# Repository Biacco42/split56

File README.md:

# split56
modulo seriese split keyboard

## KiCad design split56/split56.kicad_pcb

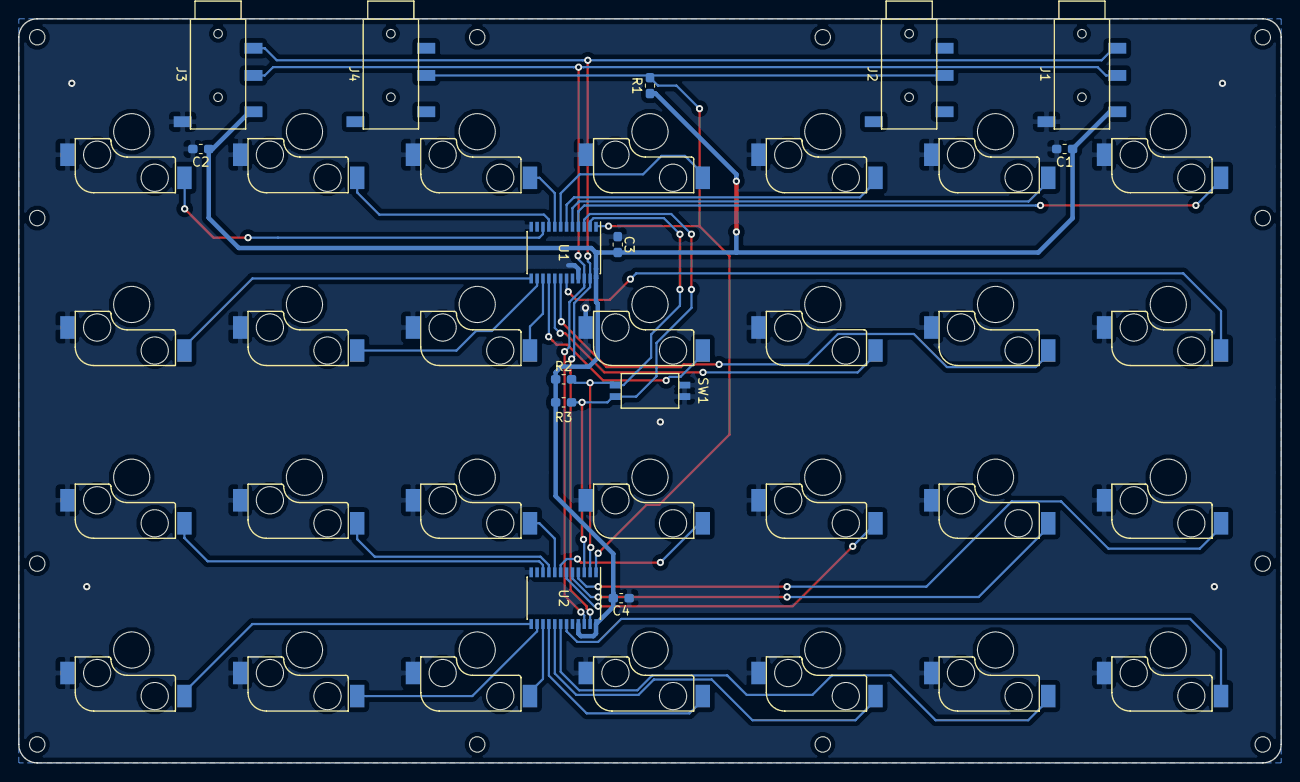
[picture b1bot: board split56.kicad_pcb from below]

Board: 2 copper layers, 139.2 x 82.0 mm, 42 parts (14 on the bottom side), 35 nets.

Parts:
C1, C2: 1 uF; C_0603_1608Metric_Pad1.05x0.95mm_HandSolder
C3, C4: 100 nF; C_0603_1608Metric_Pad1.05x0.95mm_HandSolder
J1, J2, J3, J4: AudioJack4; TRRS_SMD_PJ320
R1: 10 kΩ; R_0603_1608Metric_Pad1.05x0.95mm_HandSolder
R2, R3: 1 MΩ; R_0603_1608Metric_Pad1.05x0.95mm_HandSolder
SW1: SW_DIP_x02; DipSwitch
SW2, SW3, SW4, SW5, SW6, SW7, SW8, SW9, SW10, SW11, SW12, SW13, SW14, SW15, SW16, SW17, SW18, SW19, SW20, SW21, SW22, SW23, SW24, SW25, SW26, SW27, SW28, SW29: SW_Push; Kailh_Socket
U1, U2: TCA9555PWR; TSSOP-24_4.4x7.8mm_P0.65mm

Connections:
A1: R2.2, SW1.2, U1.2, U2.2
A2: R3.2, SW1.1, U1.3, U2.3
GND: C1.2, C2.2, C3.2, C4.2, J1.S, J3.S, SW1.3, SW1.4, SW2.1, SW3.1, SW4.1, SW5.1, SW6.1, SW7.1, SW8.1, SW9.1, SW10.1, SW11.1, SW12.1, SW13.1, SW14.1, SW15.1, SW16.1, SW17.1, SW18.1, SW19.1, SW20.1, SW21.1, SW22.1, SW23.1, SW24.1, SW25.1, SW26.1, SW27.1, SW28.1, SW29.1, U1.12, U1.21, U2.12
INT: J2.R1, J4.R1, R1.2, U1.1, U2.1
R1C1: SW2.2, U1.4
R1C2: SW6.2, U1.5
R1C3: SW10.2, U1.6
R1C4: SW14.2, U1.7
R1C5: SW18.2, U1.8
R1C6: SW22.2, U1.9
R1C7: SW26.2, U1.10
R2C1: SW3.2, U1.19
R2C2: SW7.2, U1.18
R2C3: SW11.2, U1.17
R2C4: SW15.2, U1.16
R2C5: SW19.2, U1.15
R2C6: SW23.2, U1.14
R2C7: SW27.2, U1.13
R3C1: SW4.2, U2.4
R3C2: SW8.2, U2.5
R3C3: SW12.2, U2.6
R3C4: SW16.2, U2.7
R3C5: SW20.2, U2.8
R3C6: SW24.2, U2.9
R3C7: SW28.2, U2.10
R4C1: SW5.2, U2.19
R4C2: SW9.2, U2.18
R4C3: SW13.2, U2.17
R4C4: SW17.2, U2.16
R4C5: SW21.2, U2.15
R4C6: SW25.2, U2.14
R4C7: SW29.2, U2.13
SCL: J1.R1, J3.R1, U1.22, U2.22
SDA: J1.R2, J3.R2, U1.23, U2.23
VCC: C1.1, C2.1, C3.1, C4.1, J1.T, J3.T, R1.1, R2.1, R3.1, U1.24, U2.21, U2.24

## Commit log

2019-04-10 Add split56
2019-04-10 Create LICENSE
2019-04-18 Design main circuit
2019-04-19 Add screw hole
2019-07-09 Add mount plate
2019-07-09 Add signature
2019-07-09 Implement mount plate
2019-07-09 Add bottom plate
2019-07-09 Add auxilary axis origin
2019-07-09 Add design debug data
2019-07-09 Fix mount plate hole size
2019-07-09 Add GND pour
2019-07-09 Add pdf / svg for debug
2019-07-09 Add TRRS cover
2019-07-09 Update bottom plate hole
